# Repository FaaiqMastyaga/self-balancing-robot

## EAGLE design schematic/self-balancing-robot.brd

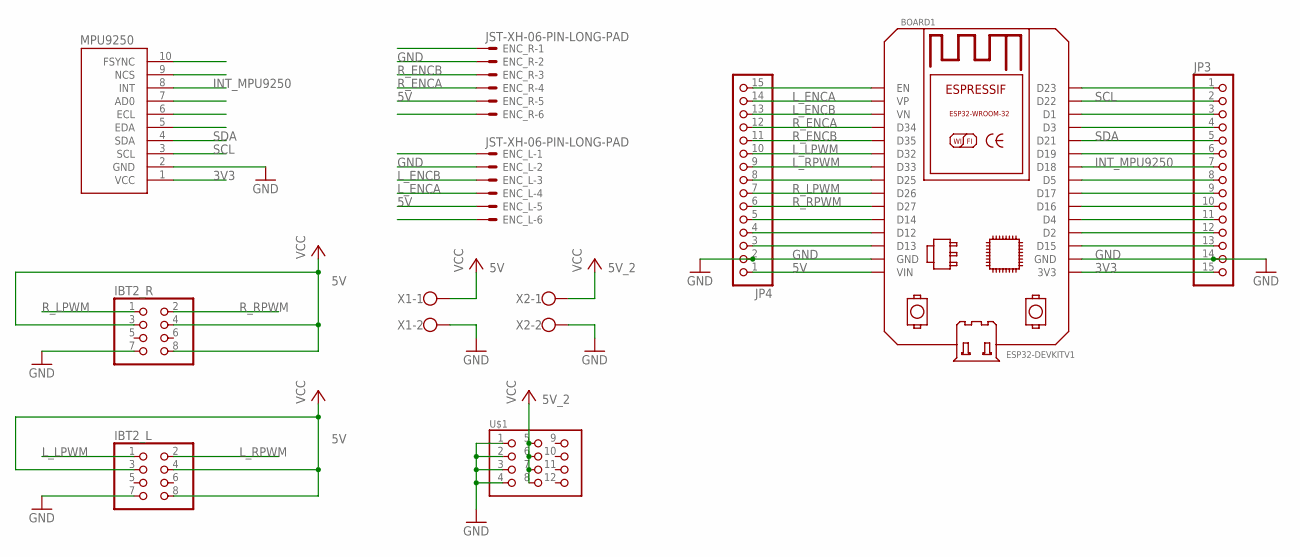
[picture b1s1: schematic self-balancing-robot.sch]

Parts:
BOARD1: ESP32DEVKITV1; ESP32-DEVKITV1
ENC_L: JST-XH-06-PIN-LONG-PAD; JST-XH-06-PACKAGE-LONG-PAD
ENC_R: JST-XH-06-PIN-LONG-PAD; JST-XH-06-PACKAGE-LONG-PAD
IBT2_L, IBT2_R: PINHD-2X4; 2X04
JP3, JP4: PINHD-1X15; 1X15
MPU9250: IMU-MODULE
U$1: PIN_3X4
X1, X2: W237-102

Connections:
3V3: BOARD1.3V3, JP3.15, MPU9250.1 (VCC)
5V: BOARD1.VIN, ENC_L.5, ENC_R.5, IBT2_L.3, IBT2_L.4, IBT2_L.8, IBT2_R.3, IBT2_R.4, IBT2_R.8, JP4.1, X1.1
5V_2: U$1.5, U$1.6, U$1.7, U$1.8, X2.1
GND: BOARD1.GND, BOARD1.GND@1 (GND), ENC_L.2, ENC_R.2, IBT2_L.7, IBT2_R.7, JP3.14, JP4.2, MPU9250.2 (GND), U$1.1, U$1.2, U$1.3, U$1.4, X1.2, X2.2
INT_MPU9250: BOARD1.D18, JP3.7, MPU9250.8 (INT)
L_ENCA: BOARD1.VP, ENC_L.4, JP4.14
L_ENCB: BOARD1.VN, ENC_L.3, JP4.13
L_LPWM: BOARD1.D32, IBT2_L.1, JP4.10
L_RPWM: BOARD1.D33, IBT2_L.2, JP4.9
unnamed: BOARD1.D23, JP3.1
unnamed: BOARD1.D1, JP3.3
unnamed: BOARD1.D3, JP3.4
unnamed: BOARD1.D19, JP3.6
unnamed: BOARD1.D5, JP3.8
unnamed: BOARD1.D17, JP3.9
unnamed: BOARD1.D16, JP3.10
unnamed: BOARD1.D4, JP3.11
unnamed: BOARD1.D2, JP3.12
unnamed: BOARD1.D15, JP3.13
unnamed: BOARD1.EN, JP4.15
unnamed: BOARD1.D25, JP4.8
unnamed: BOARD1.D14, JP4.5
unnamed: BOARD1.D12, JP4.4
unnamed: BOARD1.D13, JP4.3
R_ENCA: BOARD1.D34, ENC_R.4, JP4.12
R_ENCB: BOARD1.D35, ENC_R.3, JP4.11
R_LPWM: BOARD1.D26, IBT2_R.1, JP4.7
R_RPWM: BOARD1.D27, IBT2_R.2, JP4.6
SCL: BOARD1.D22, JP3.2, MPU9250.3 (SCL)
SDA: BOARD1.D21, JP3.5, MPU9250.4 (SDA)

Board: 2 copper layers, 11 parts (0 on the bottom side), 30 nets, no tracks yet.

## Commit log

2025-02-24 feat: add full system source code
2025-02-24 feat: add pid library
2025-02-24 feat: add electrical system schematic
2025-02-24 refactor: move source code to anothe directory
